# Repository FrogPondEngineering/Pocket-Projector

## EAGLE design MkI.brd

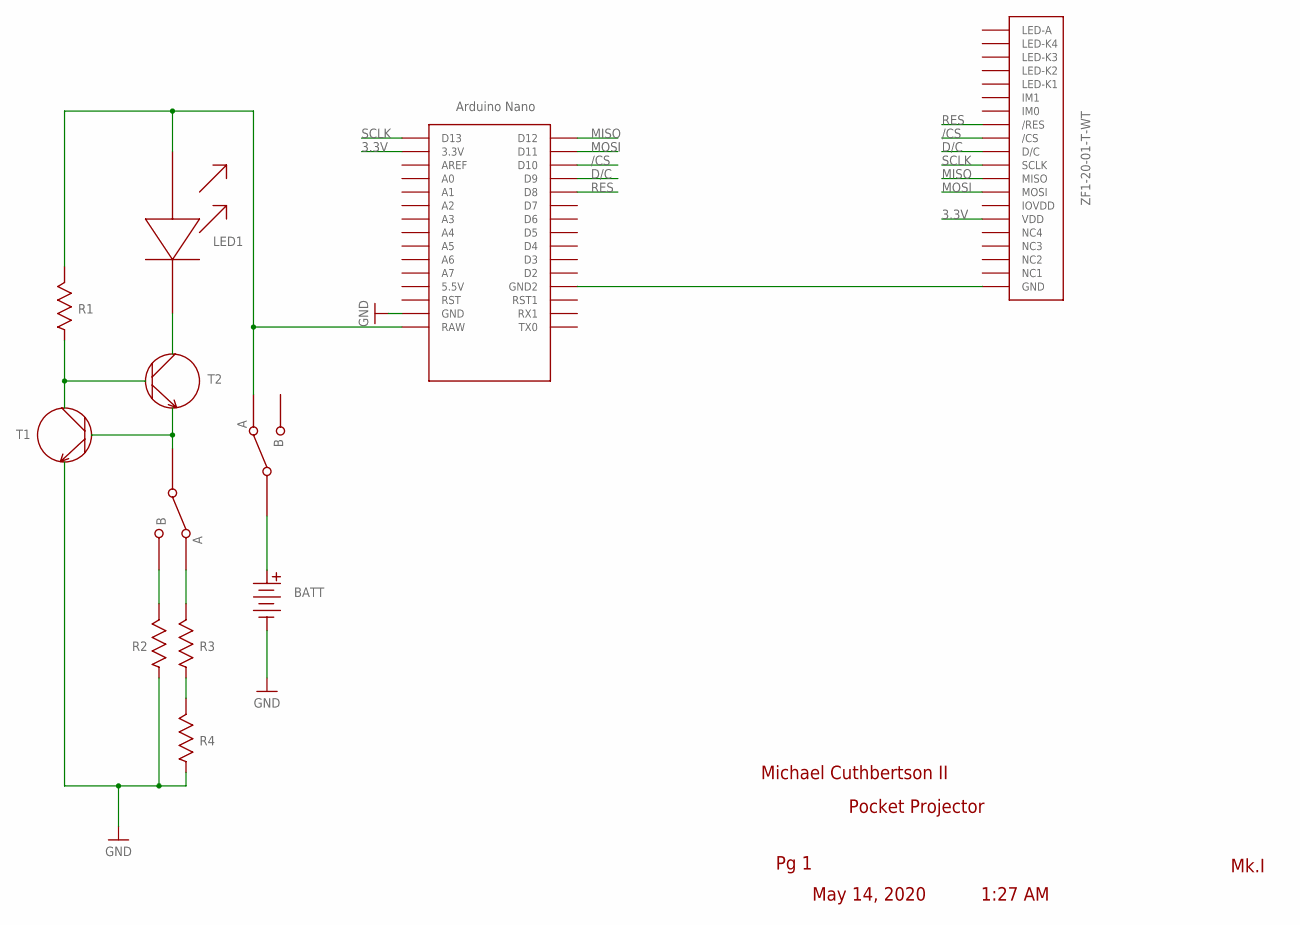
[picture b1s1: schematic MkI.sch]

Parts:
R1: 2.2k; ERJ1T
R2: 130; CRCW2512
R3, R4: 200; CRCW2512
S1, S2: A107673-ND
T1: BC547
T2: BD139
U$1: NANO
U$3: XHGAWT-00-0000-00000HXE1
U$5: 9v; BATT
U$6: ZF1-20-01-T-WT

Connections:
3.3V: U$1.3.3V, U$6.VDD
/CS: U$1.D10, U$6./CS
D/C: U$1.D9, U$6.D/C
GND: R2.P$1, R4.P$1, T1.P$3, U$1.GND, U$5.GND
MISO: U$1.D12, U$6.MISO
MOSI: U$1.D11, U$6.MOSI
unnamed: T2.P$2, U$3.P$1
unnamed: S2.P$1, T1.P$1, T2.P$3
unnamed: R1.P$1, T1.P$2, T2.P$1
unnamed: R3.P$1, R4.P$2
unnamed: R1.P$2, S1.P$2, U$1.RAW, U$3.P$2
unnamed: R2.P$2, S2.P$3
unnamed: R3.P$2, S2.P$2
unnamed: S1.P$1, U$5.VCC
unnamed: U$1.GND1 (GND2), U$6.GND
RES: U$1.D8, U$6./RES
SCLK: U$1.D13, U$6.SCLK

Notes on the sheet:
May 14, 2020
1:27 AM
Pg 1
Mk.I
Pocket Projector
Michael Cuthbertson II
LED1
BATT

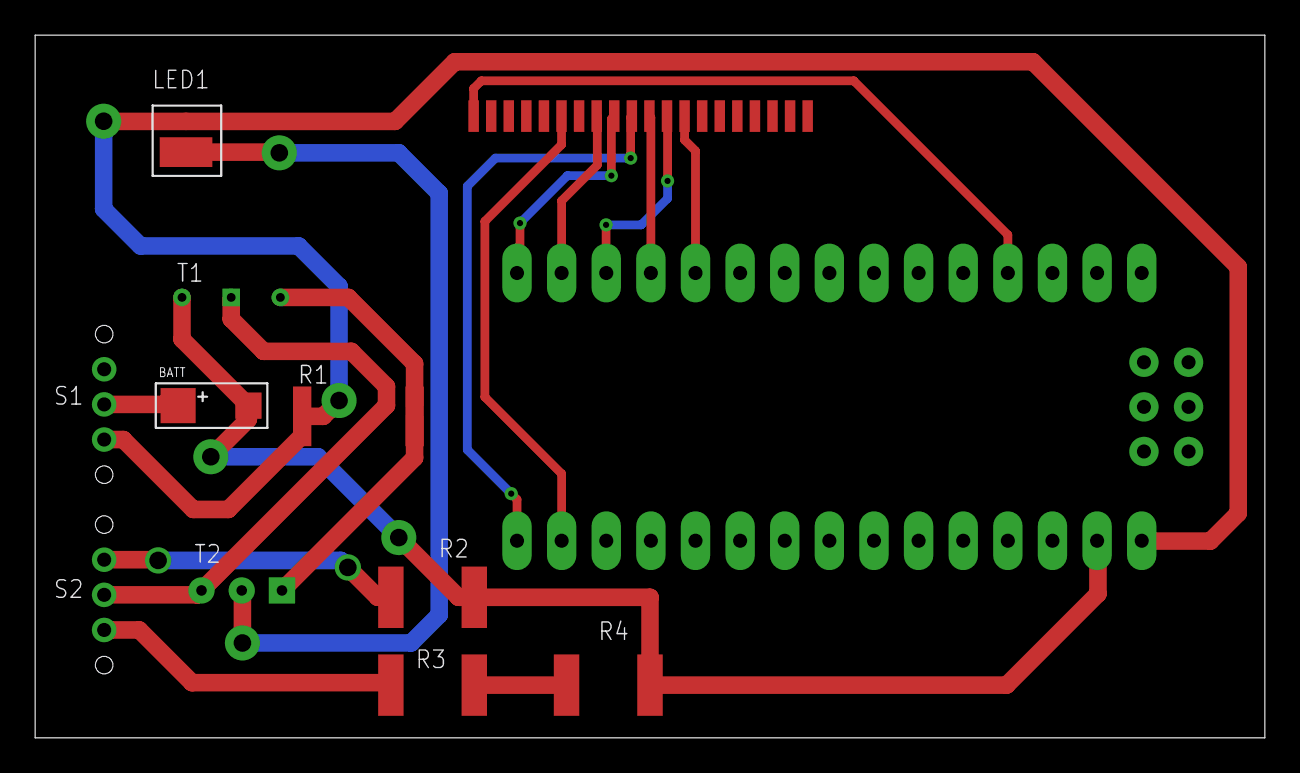
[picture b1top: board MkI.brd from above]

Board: 2 copper layers, 70.0 x 40.0 mm, 12 parts (0 on the bottom side), 17 nets.

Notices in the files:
parts and their libraries:
SparkFun-PowerSymbols: Licensing: Creative Commons ShareAlike 4.0 International - https://creativecommons.org/licenses/by-sa/4.0
